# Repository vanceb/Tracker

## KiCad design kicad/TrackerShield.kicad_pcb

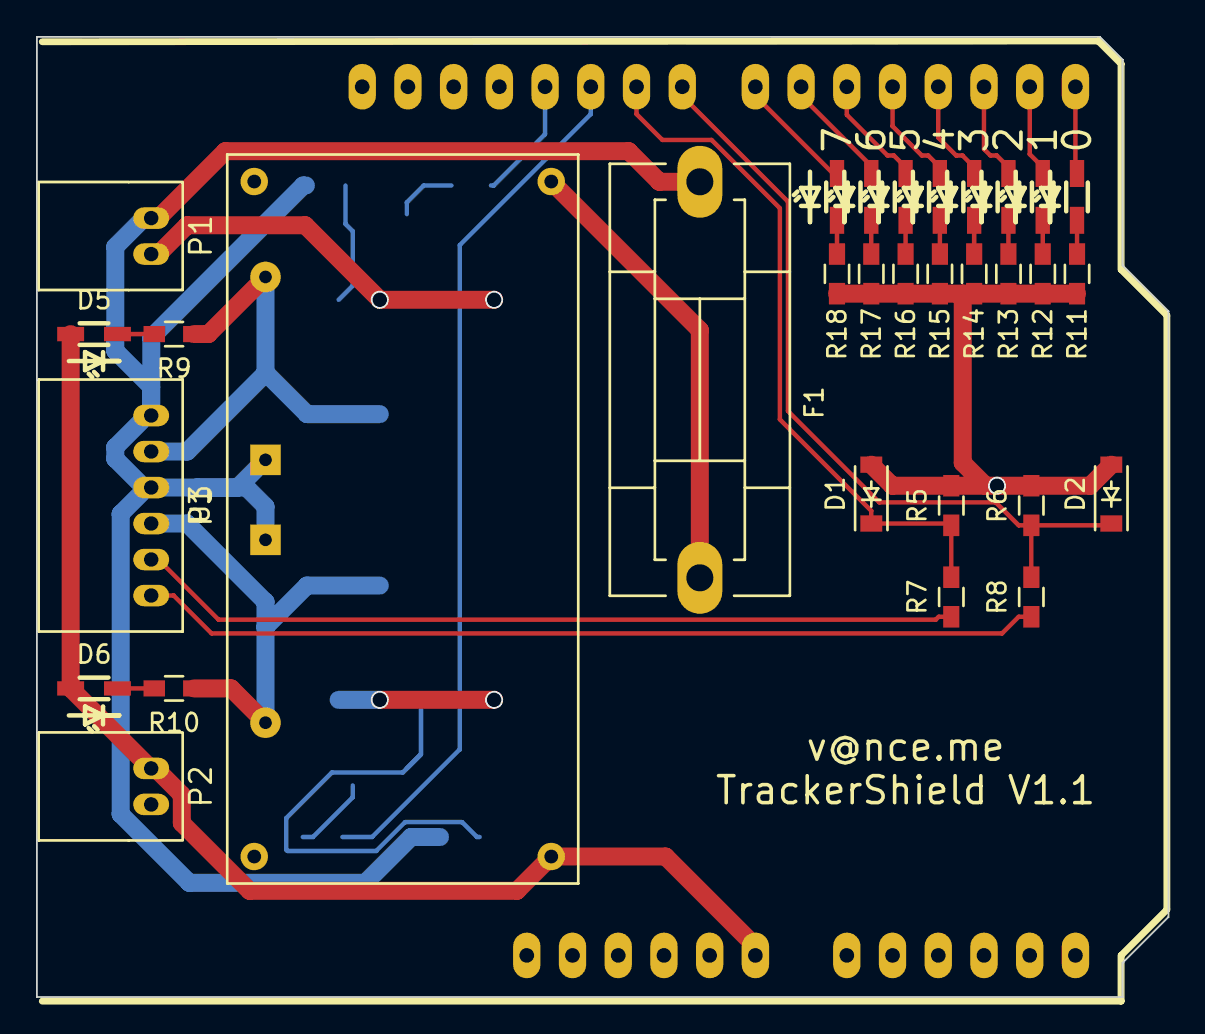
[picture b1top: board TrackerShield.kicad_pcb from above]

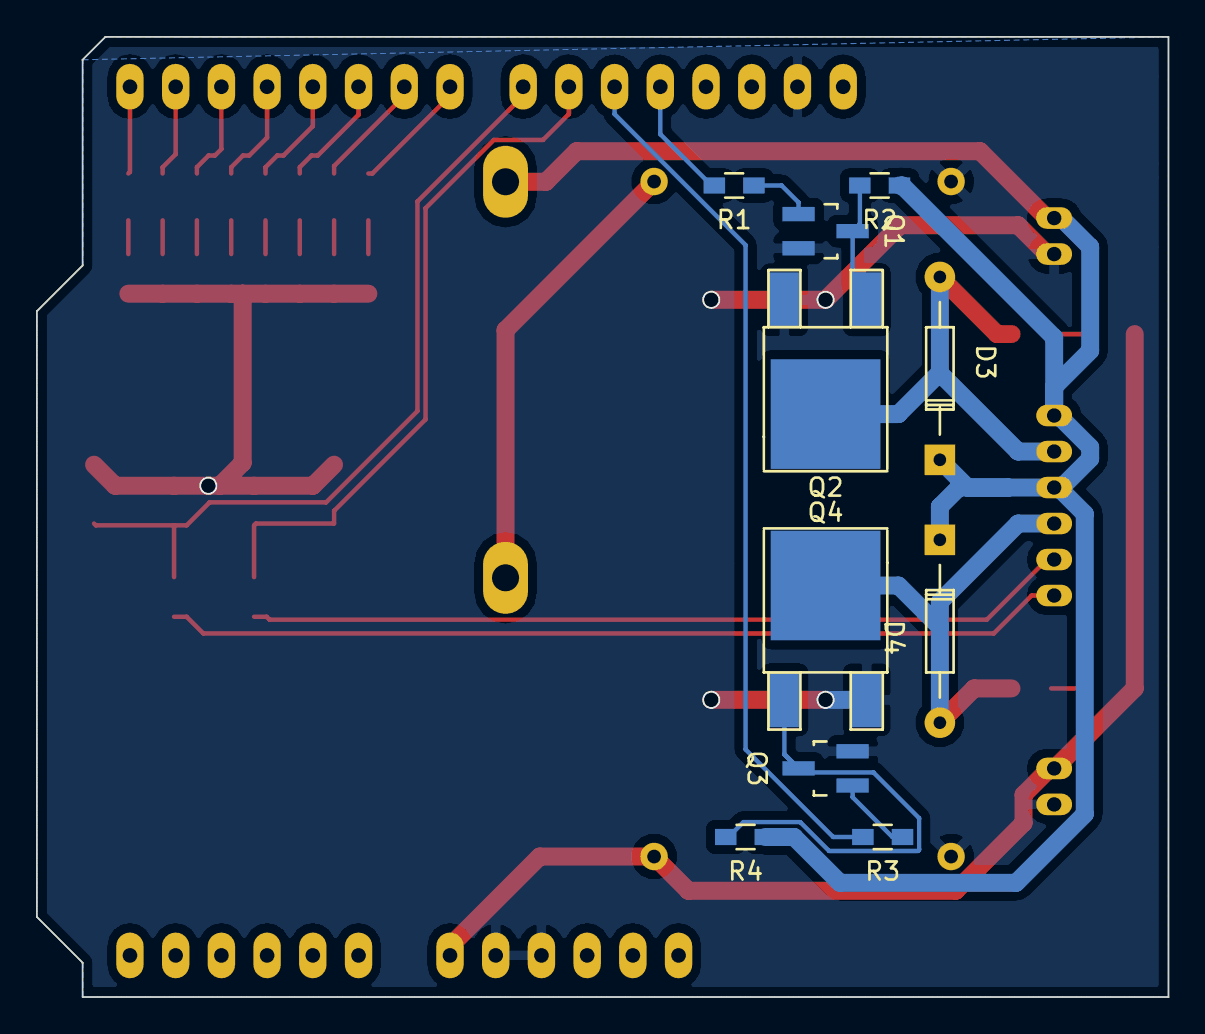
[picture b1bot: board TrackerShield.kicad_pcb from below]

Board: 2 copper layers, 62.9 x 53.3 mm, 42 parts (10 on the bottom side), 34 nets.

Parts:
D1, D2: 5.1V; SOD-123
D3, D4: D; Diode_DO-35_SOD27_Horizontal_RM10
D5, D6, D7, D8, D9, D10, D11, D12, D13, D14: LED; LED_SMD_1.6x0.8mm
F1: FUSE; Fuseholder5x20_horiz_SemiClosed_Casing10x25mm
P1: PWR_IN; JST-2RA
P2: PWR_OUT; JST-2RA
P3: MAIN_IO; JST-6RA
Q1, Q3: BC848B; SOT-23_Handsoldering
Q2, Q4: Std12nf06lt4; TO-252-2Lead
R1, R2, R3, R4, R7, R8: 10k; R_0603_HandSoldering
R5, R6: 3k3; R_0603_HandSoldering
R9, R10, R11, R12, R13, R14, R15, R16, R17, R18: 220; R_0603_HandSoldering
SHIELD1: ARDUINO_SHIELD; ARDUINO_SHIELD_SHORT
U1: Buck_Converter

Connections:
+5VP: D5.2, D6.2, P2.1, SHIELD1.V_IN, U1.3
GND: D1.2, D2.2, P1.2, P2.2, Q1.2, Q2.3, Q3.2, Q4.3, R5.2, R6.2, R11.1, R12.1, R13.1, R14.1, R15.1, R16.1, R17.1, R18.1, SHIELD1.GND1, SHIELD1.GND2, SHIELD1.GND3, U1.2, U1.4
unnamed: D1.1, R5.1, R7.2, SHIELD1.9
unnamed: D2.1, R6.1, R8.2, SHIELD1.8
unnamed: D3.1, D4.1, F1.1, P1.1, P3.1, P3.3, R2.1, R4.1
unnamed: D3.2, P3.2, Q2.2, R9.1
unnamed: D4.2, P3.4, Q4.2, R10.1
unnamed: D5.1, R9.2
unnamed: D6.1, R10.2
unnamed: D7.1, R11.2
unnamed: D7.2, SHIELD1.0
unnamed: D8.1, R12.2
unnamed: D8.2, SHIELD1.1
unnamed: D9.1, R13.2
unnamed: D9.2, SHIELD1.2
unnamed: D10.1, R14.2
unnamed: D10.2, SHIELD1.3
unnamed: D11.1, R15.2
unnamed: D11.2, SHIELD1.4
unnamed: D12.1, R16.2
unnamed: D12.2, SHIELD1.5
unnamed: D13.1, R17.2
unnamed: D13.2, SHIELD1.6
unnamed: D14.1, R18.2
unnamed: D14.2, SHIELD1.7
unnamed: F1.2, U1.1
unnamed: P3.5, R7.1
unnamed: P3.6, R8.1
unnamed: Q1.1, R1.1
unnamed: Q1.3, Q2.1, R2.2
unnamed: Q3.1, R3.1
unnamed: Q3.3, Q4.1, R4.2
unnamed: R1.2, SHIELD1.11
unnamed: R3.2, SHIELD1.10

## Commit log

2016-05-11 Tweaked .gitignore
2016-05-13 Added DB9 Pinout details
2016-05-17 Added some documentation and suggested improvements
2016-06-12 Tested and failed to switch output FET. Shield redesigned to provide transistor switching of FET. Buck converter and fuse moved to allow internal antennas to be fitted without interference
2016-06-26 Redesigned board submitted for manufacture
2016-07-12 General update - lots of rubbish unable to get AWS_IOT working reliably, but mqtt works fine
2016-07-12 removed .DS_Store
